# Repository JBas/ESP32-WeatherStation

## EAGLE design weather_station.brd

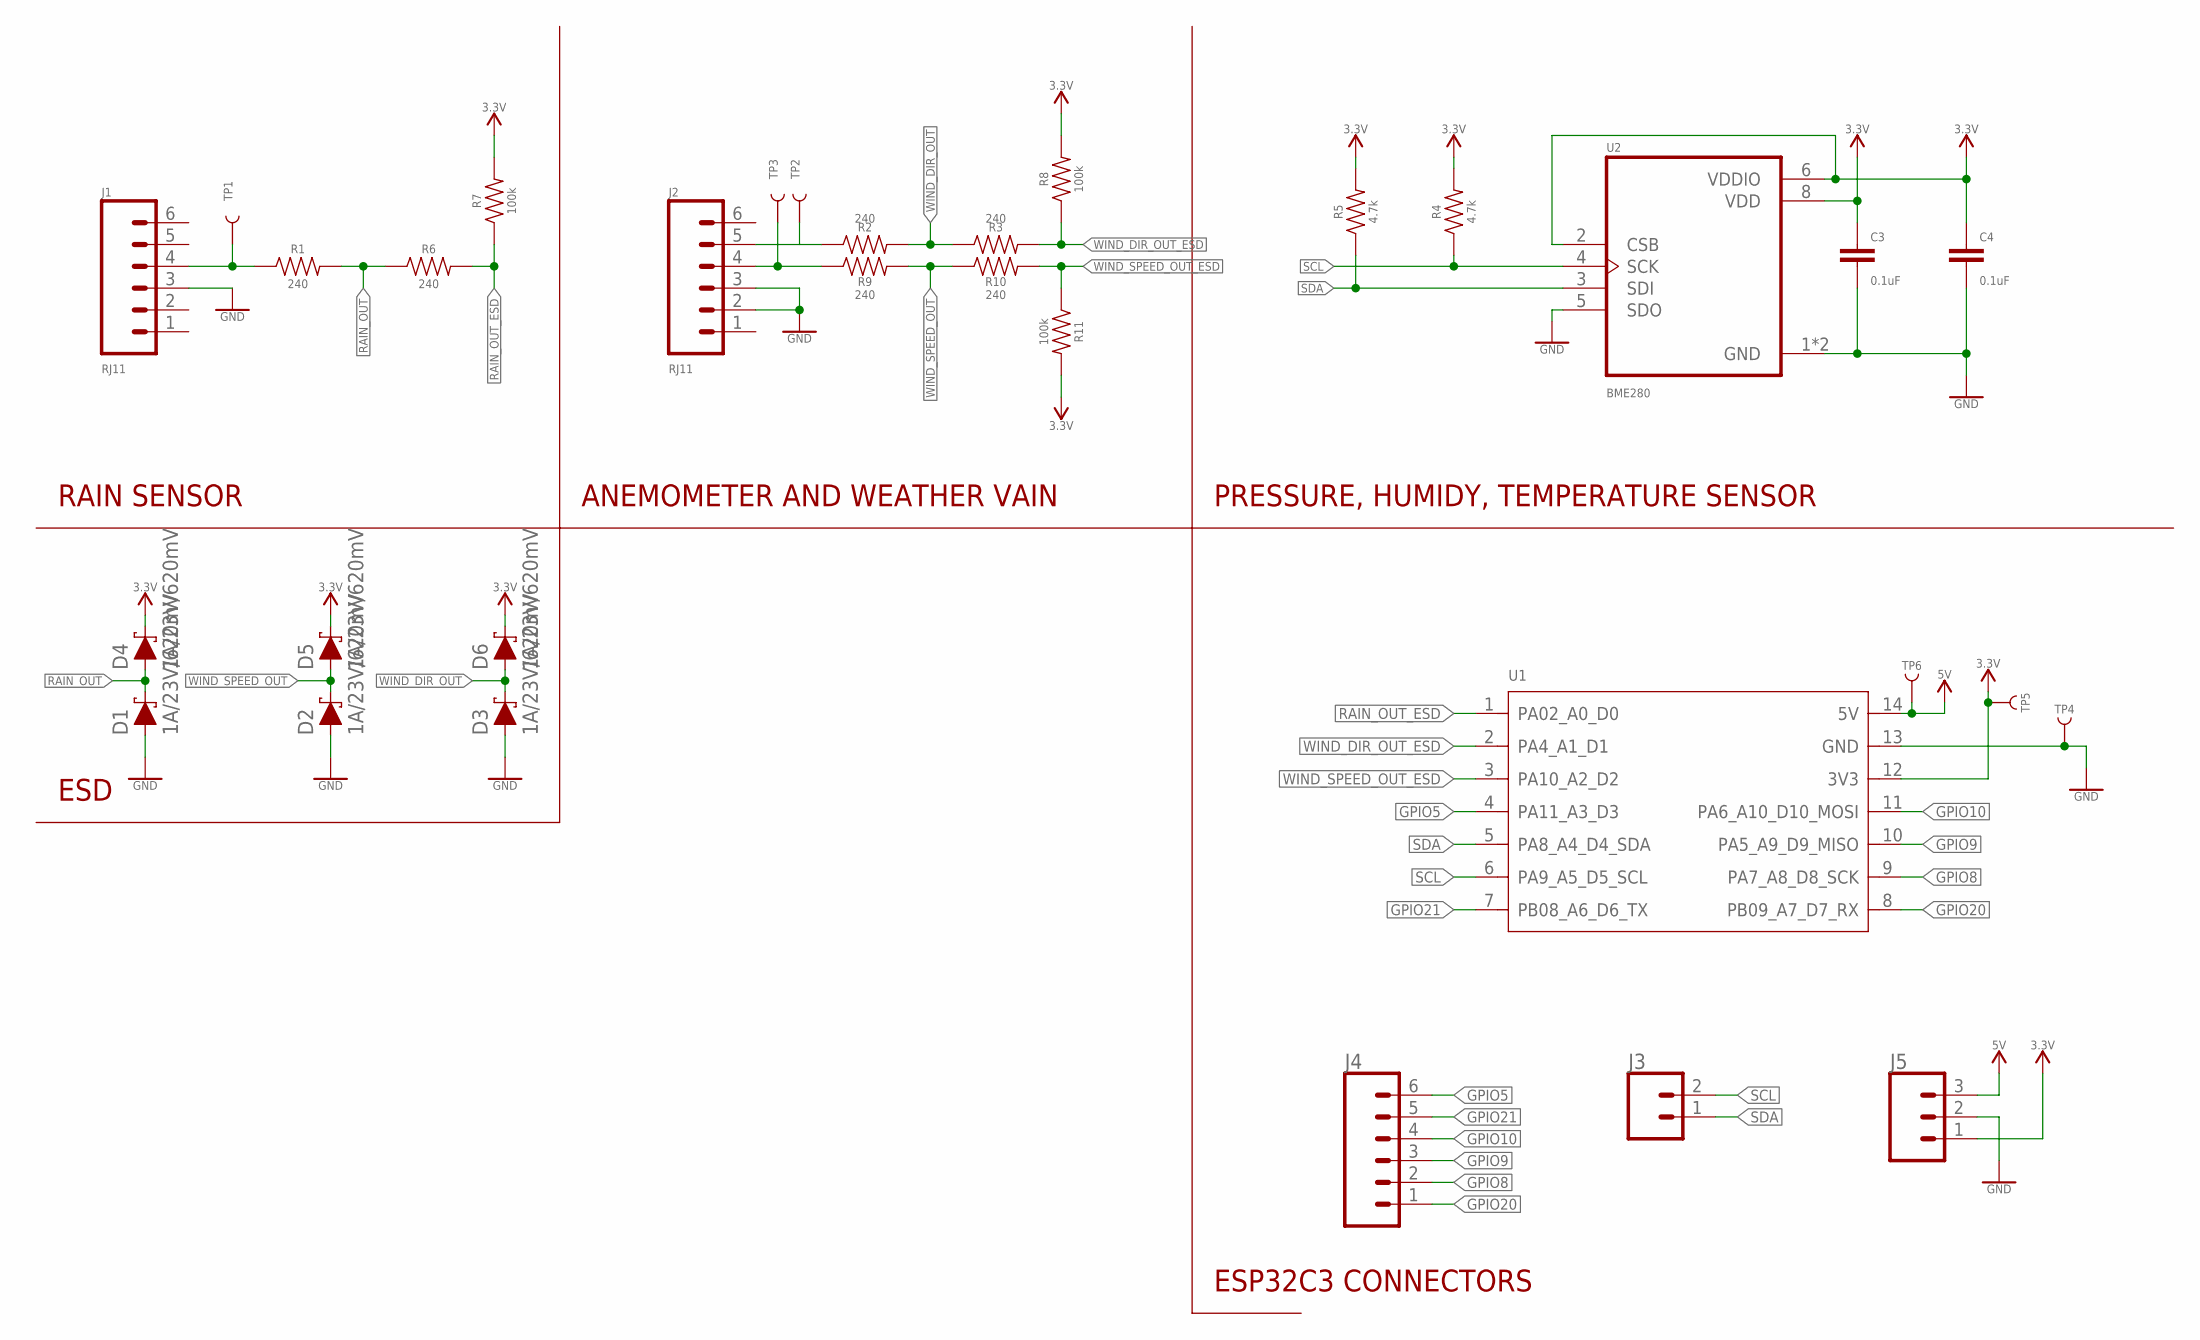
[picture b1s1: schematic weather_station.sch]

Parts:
C3, C4: 0.1uF; 0603
D1, D2, D3, D4, D5, D6: 1A/23V/620mV; SOD-323
J1, J2: RJ11; RJ11-6
J3: CONN_02; 1X02
J4: CONN_06SILK_FEMALE_PTH; 1X06
J5: CONN_03; 1X03
R1, R2, R3, R6, R9, R10: 240; 0603
R4, R5: 4.7k; 0603
R7, R8, R11: 100k; 0603
TP1, TP2, TP3, TP4, TP5, TP6: TEST-POINT3; PAD.03X.03
U1: MODULE-SEEEDUINO-XIAO-ESP32C3-PIN; MODULE14P-2.54-21X17.8MM
U2: BME280; PSON65P250X250X100-8N

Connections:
3.3V: C3.1, C4.1, D4.C, D5.C, D6.C, J5.1, R4.2, R5.2, R7.2, R8.2, R11.2, TP5.P$1, U1.12 (3V3), U2.2 (CSB), U2.6 (VDDIO), U2.8 (VDD)
5V: J5.3, TP6.P$1, U1.14 (5V)
GND: C3.2, C4.2, D1.A, D2.A, D3.A, J1.3, J2.2, J2.3, J5.2, TP4.P$1, U1.13 (GND), U2.1 (GND), U2.5 (SDO), U2.7 (GND)
GPIO5: J4.6, U1.4 (PA11_A3_D3)
GPIO8: J4.2, U1.9 (PA7_A8_D8_SCK)
GPIO9: J4.3, U1.10 (PA5_A9_D9_MISO)
GPIO10: J4.4, U1.11 (PA6_A10_D10_MOSI)
GPIO20: J4.1, U1.8 (PB09_A7_D7_RX)
GPIO21: J4.5, U1.7 (PB08_A6_D6_TX)
RAIN_OUT: D1.C, D4.A, R1.2, R6.1
RAIN_OUT_ESD: R6.2, R7.1, U1.1 (PA02_A0_D0)
RAIN_RAW: J1.4, R1.1, TP1.P$1
SCL: J3.2, R4.1, U1.6 (PA9_A5_D5_SCL), U2.4 (SCK)
SDA: J3.1, R5.1, U1.5 (PA8_A4_D4_SDA), U2.3 (SDI)
WIND_DIR_OUT: D3.C, D6.A, R2.2, R3.1
WIND_DIR_OUT_ESD: R3.2, R8.1, U1.2 (PA4_A1_D1)
WIND_DIR_RAW: J2.5, R2.1, TP2.P$1
WIND_SPEED_OUT: D2.C, D5.A, R9.2, R10.1
WIND_SPEED_OUT_ESD: R10.2, R11.1, U1.3 (PA10_A2_D2)
WIND_SPEED_RAW: J2.4, R9.1, TP3.P$1

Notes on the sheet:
RAIN SENSOR
ANEMOMETER AND WEATHER VAIN
PRESSURE, HUMIDY, TEMPERATURE SENSOR
ESD
ESP32C3 CONNECTORS

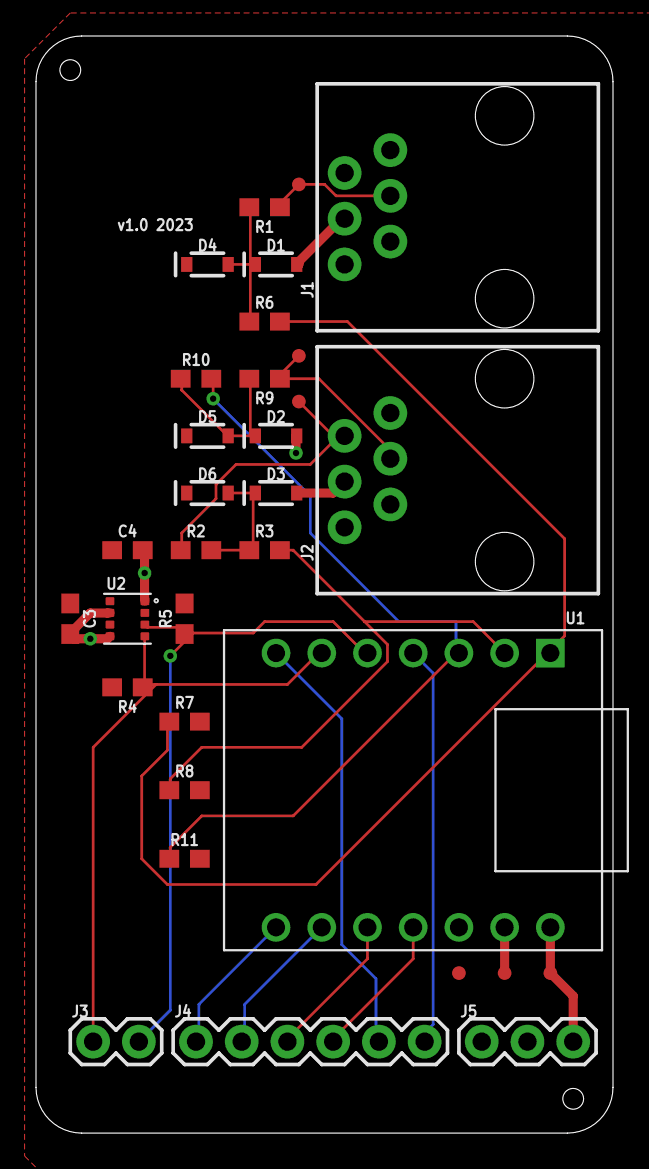
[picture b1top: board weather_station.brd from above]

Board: 2 copper layers, 32.1 x 60.9 mm, 32 parts (0 on the bottom side), 20 nets.

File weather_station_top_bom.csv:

Comment,Designator,Footprint,LCSC Part #
0.1uF,C3 C4,0603,
1A/23V/620mV,D1 D2 D3 D4 D5 D6,SOD-323,
4.7k,R4 R5,0603,
100k,R7 R8 R11,0603,
240,R1 R2 R3 R6 R9 R10,0603,
BME280,U2,PSON65P250X250X100-8N,

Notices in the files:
parts and their libraries:
SparkFun-Capacitors: Licensing: Creative Commons ShareAlike 4.0 International - https://creativecommons.org/licenses/by-sa/4.0
